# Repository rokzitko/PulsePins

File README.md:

# PulsePins Pulse Sequencer

PulsePins is an open-hardware FPGA pulse sequencer for laboratory timing and digital control. The released DE10-Nano design provides 32 digital outputs and a 10 ns programmable time step at a 100 MHz streamer clock. Use it for triggers, gates, digital buses, and DAC or DDS control; it does not generate analog or RF waveforms directly.

## Start here

Choose the path that matches what you want to do first:

| Goal | Start here |
| ---- | ---------- |
| Bring up a DE10-Nano | [Quick start](docs/docs/quick_start.md) |
| Choose a command or API | [Tool chooser](docs/docs/choose_tool.md) |
| Follow a complete lab workflow | [Worked examples](docs/docs/examples.md) |
| Understand the sequencer | [Sequencer model](docs/docs/sequencer_model.md) |
| Modify or extend PulsePins | [Hacking guide](HACKING.md) and [extension cookbook](docs/docs/extension_cookbook.md) |

## At a glance

| Item | Released DE10-Nano design |
| ---- | ------------------------- |
| Digital output | 32-bit bus, 3.3 V LVTTL |
| Timing | 10 ns programmable time step at a 100 MHz streamer clock |
| Sequence delivery | HPS-driven FIFO or memory-backed DMA transfers up to 512 MB |
| Control | Command-line tools, C++, Python, SCPI-style TCP, and a browser interface |
| Checks | FPGA readback encoder, CRC and FIFO diagnostics, and board self-tests |
| Design files | SystemVerilog/Verilog RTL, software, and KiCad sources under the MIT License |

## Documentation

[User and reference manual](http://auger.ijs.si/pulsepins/site/) ([source](docs/docs/index.md))

Useful contributor documents:

* [Hacking guide](HACKING.md)
* [Contribution guide](CONTRIBUTING.md)
* [Build and deployment](docs/docs/build.md)
* [Development guide](docs/docs/hacking.md)

## Recipes

Reusable command examples for the PulsePins command-line tools are stored in [`recipes/`](recipes/).
These files are separate from `tests/` so test executables and example command invocations are easier to find.

## License

This project is released under the MIT License. You may use, copy, modify, merge, publish, distribute, sublicense,
and/or sell the software and FPGA firmware (including RTL sources and generated bitstreams), including in commercial
and closed-source products. The only conditions are that you preserve the original copyright and license notice in all
substantial portions of the software/firmware, and that the software and firmware are provided “as is”, without any
warranty or liability on the part of the authors.

If you use PulsePins in scientific work, please cite:

> R. Žitko, *PulsePins: Open-hardware digital pulse sequencer for time-resolved experiments*, Zenodo (2025), [doi:10.5281/zenodo.17903233](https://doi.org/10.5281/zenodo.17903233).

### BibTeX

```bibtex
@misc{pulsepins_1_0,
  author       = {Žitko, Rok},
  title        = {PulsePins: Open-hardware digital pulse sequencer for time-resolved experiments},
  year         = {2025},
  publisher    = {Zenodo},
  version      = {1.0},
  doi          = {10.5281/zenodo.17903233},
  url          = {https://doi.org/10.5281/zenodo.17903233}
}
```

## Acknowledgments

This project incorporates code from the project [rsyocto](https://github.com/robseb/rsyocto) (c) Robin Sebastian, licensed under the MIT License.
See `third_party/rsyocto/LICENSE` for details.

[Rok Zitko](http://auger.ijs.si/nano), [rok.zitko@ijs.si](mailto:rok.zitko+pulsepins@ijs.si), 2025

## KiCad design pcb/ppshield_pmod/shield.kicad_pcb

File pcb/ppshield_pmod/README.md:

## PulsePins shield with Pmod ports

Features:

 -   all signals on connectors have ESD protection diodes
 -   SMA connectors for external clock and for pulse-per-second (PPS) signals; monitoring LED for PPS signal; optional built-in 50 Ω terminators
 -   SMA connector for one trigger signal; it is connected to a fast comparator with a tunable reference voltage; optional 50 Ω terminator; monitoring LED
 -   two output signals, Q0 and Q1, are buffered and wired to SMA connectors; monitoring LEDs
 -   Status LEDs: trigger armed, trigger activated, done, buffer error
 -   Activity & heartbeat LEDs
 -   Qwiic I2C connector for external modules
 -   Optional temperature monitor (I2C interface)
 -   Optional 16-bit DAC (I2C interface) with a separate low-noise power supply (a possible application is frequency tuning of an OCXO; with PPS from a GNSS receiver, this can form a simple GPS-disciplined oscillator (GPSDO))
 -   Test points for troubleshooting

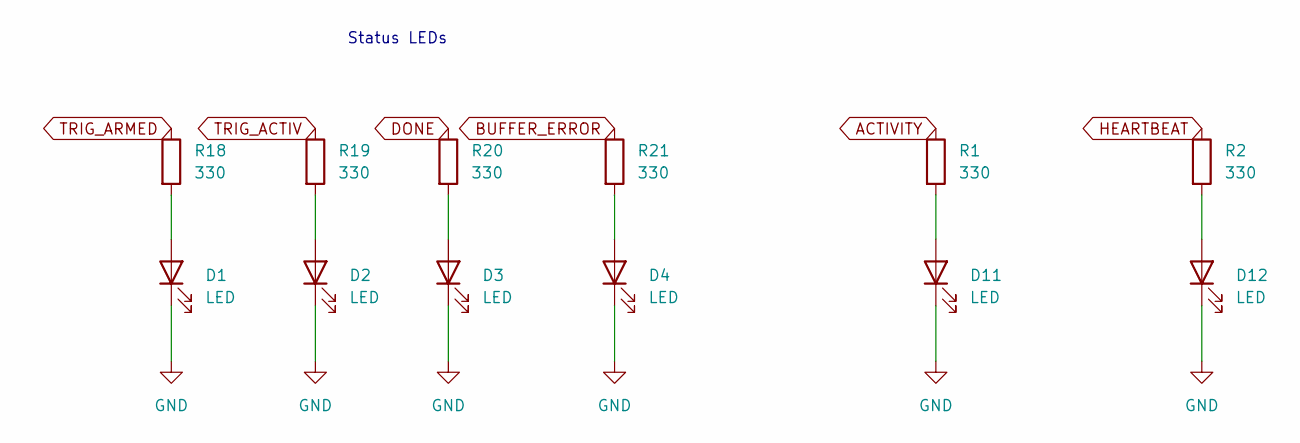
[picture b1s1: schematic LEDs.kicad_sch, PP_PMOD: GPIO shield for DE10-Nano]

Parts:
D1, D2, D3, D4, D11, D12: LED; LED_0603_1608Metric_Pad1.05x0.95mm_HandSolder
R1, R2, R18, R19, R20, R21: 330; R_0603_1608Metric_Pad0.98x0.95mm_HandSolder

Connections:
ACTIVITY: R1.1; also elsewhere on the board
BUFFER_ERROR: R21.1; also elsewhere on the board
DONE: R20.1; also elsewhere on the board
GND: D1.1 (K), D2.1 (K), D3.1 (K), D4.1 (K), D11.1 (K), D12.1 (K); also elsewhere on the board
HEARTBEAT: R2.1; also elsewhere on the board
unnamed: D1.2 (A), R18.2
unnamed: D2.2 (A), R19.2
unnamed: D3.2 (A), R20.2
unnamed: D4.2 (A), R21.2
unnamed: D11.2 (A), R1.2
unnamed: D12.2 (A), R2.2
TRIG_ACTIV: R19.1; also elsewhere on the board
TRIG_ARMED: R18.1; also elsewhere on the board

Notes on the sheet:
Status LEDs

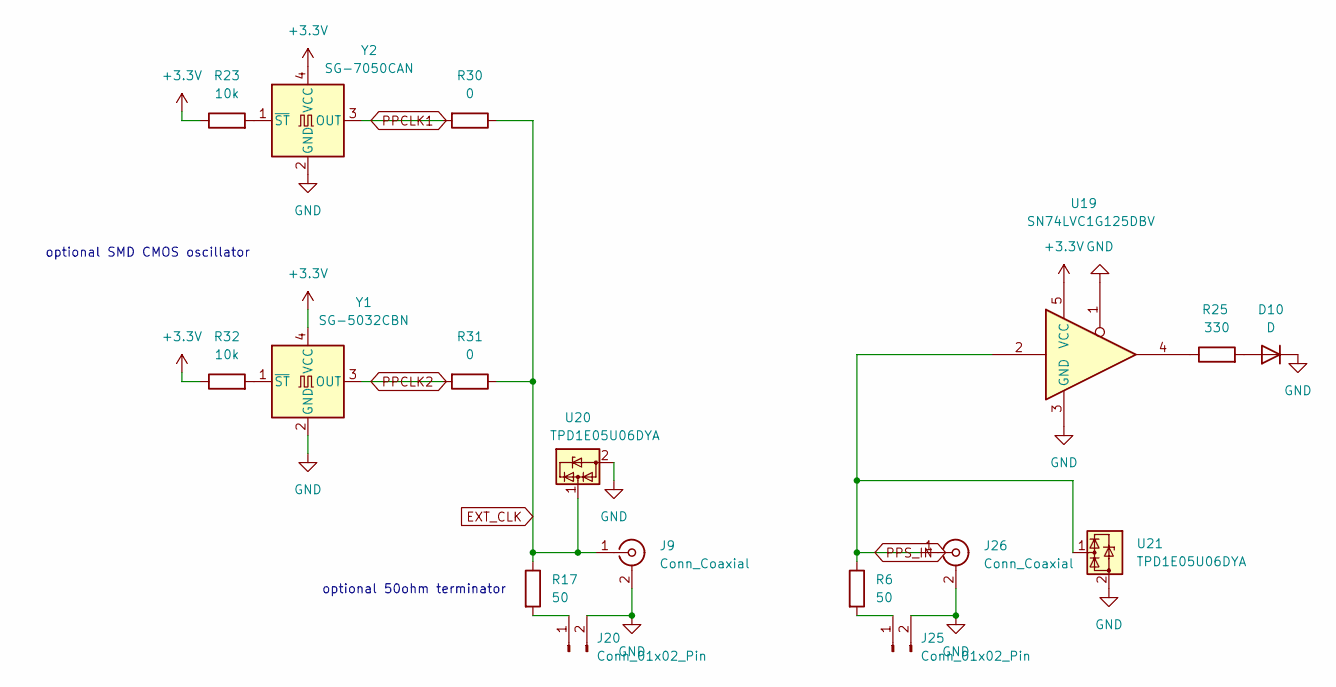
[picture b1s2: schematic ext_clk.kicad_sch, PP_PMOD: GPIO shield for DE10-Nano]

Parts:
D10: D; LED_0603_1608Metric_Pad1.05x0.95mm_HandSolder
J9, J26: Conn_Coaxial; SMA_Amphenol_132134-16_Vertical
J20, J25: Conn_01x02_Pin; PinHeader_1x02_P2.00mm_Vertical
R6, R17: 50; R_0603_1608Metric_Pad0.98x0.95mm_HandSolder
R23, R32: 10k; R_0603_1608Metric_Pad0.98x0.95mm_HandSolder
R25: 330; R_0603_1608Metric_Pad0.98x0.95mm_HandSolder
R30, R31: 0; R_0402_1005Metric_Pad0.72x0.64mm_HandSolder
U19: SN74LVC1G125DBV; SOT-23-5
U20, U21: TPD1E05U06DYA; D_SOD-523
Y1: SG-5032CBN; Crystal_SMD_5032-4Pin_5.0x3.2mm
Y2: SG-7050CAN; Oscillator_SMD_SeikoEpson_SG8002CA-4Pin_7.0x5.0mm

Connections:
+3.3V: R23.1, R32.1, U19.5 (VCC), Y1.4 (VCC), Y2.4 (VCC); also elsewhere on the board
EXT_CLK: J9.1 (In), R17.1, R30.1, R31.1, U20.1 (I/O); also elsewhere on the board
GND: D10.1 (K), J9.2 (Ext), J20.2, J25.2, J26.2 (Ext), U19.1, U19.3 (GND), U20.2 (GND), U21.2 (GND), Y1.2 (GND), Y2.2 (GND); also elsewhere on the board
unnamed: D10.2 (A), R25.2
unnamed: J20.1, R17.2
unnamed: J25.1, R6.2
unnamed: R25.1, U19.4
unnamed: R32.2, Y1.1 (~ST)
unnamed: R23.2, Y2.1 (~ST)
PPCLK1: R30.2, Y2.3 (OUT); also elsewhere on the board
PPCLK2: R31.2, Y1.3 (OUT); also elsewhere on the board
PPS_IN: J26.1 (In), R6.1, U19.2, U21.1 (I/O); also elsewhere on the board

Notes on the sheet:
optional 50ohm terminator
optional SMD CMOS oscillator

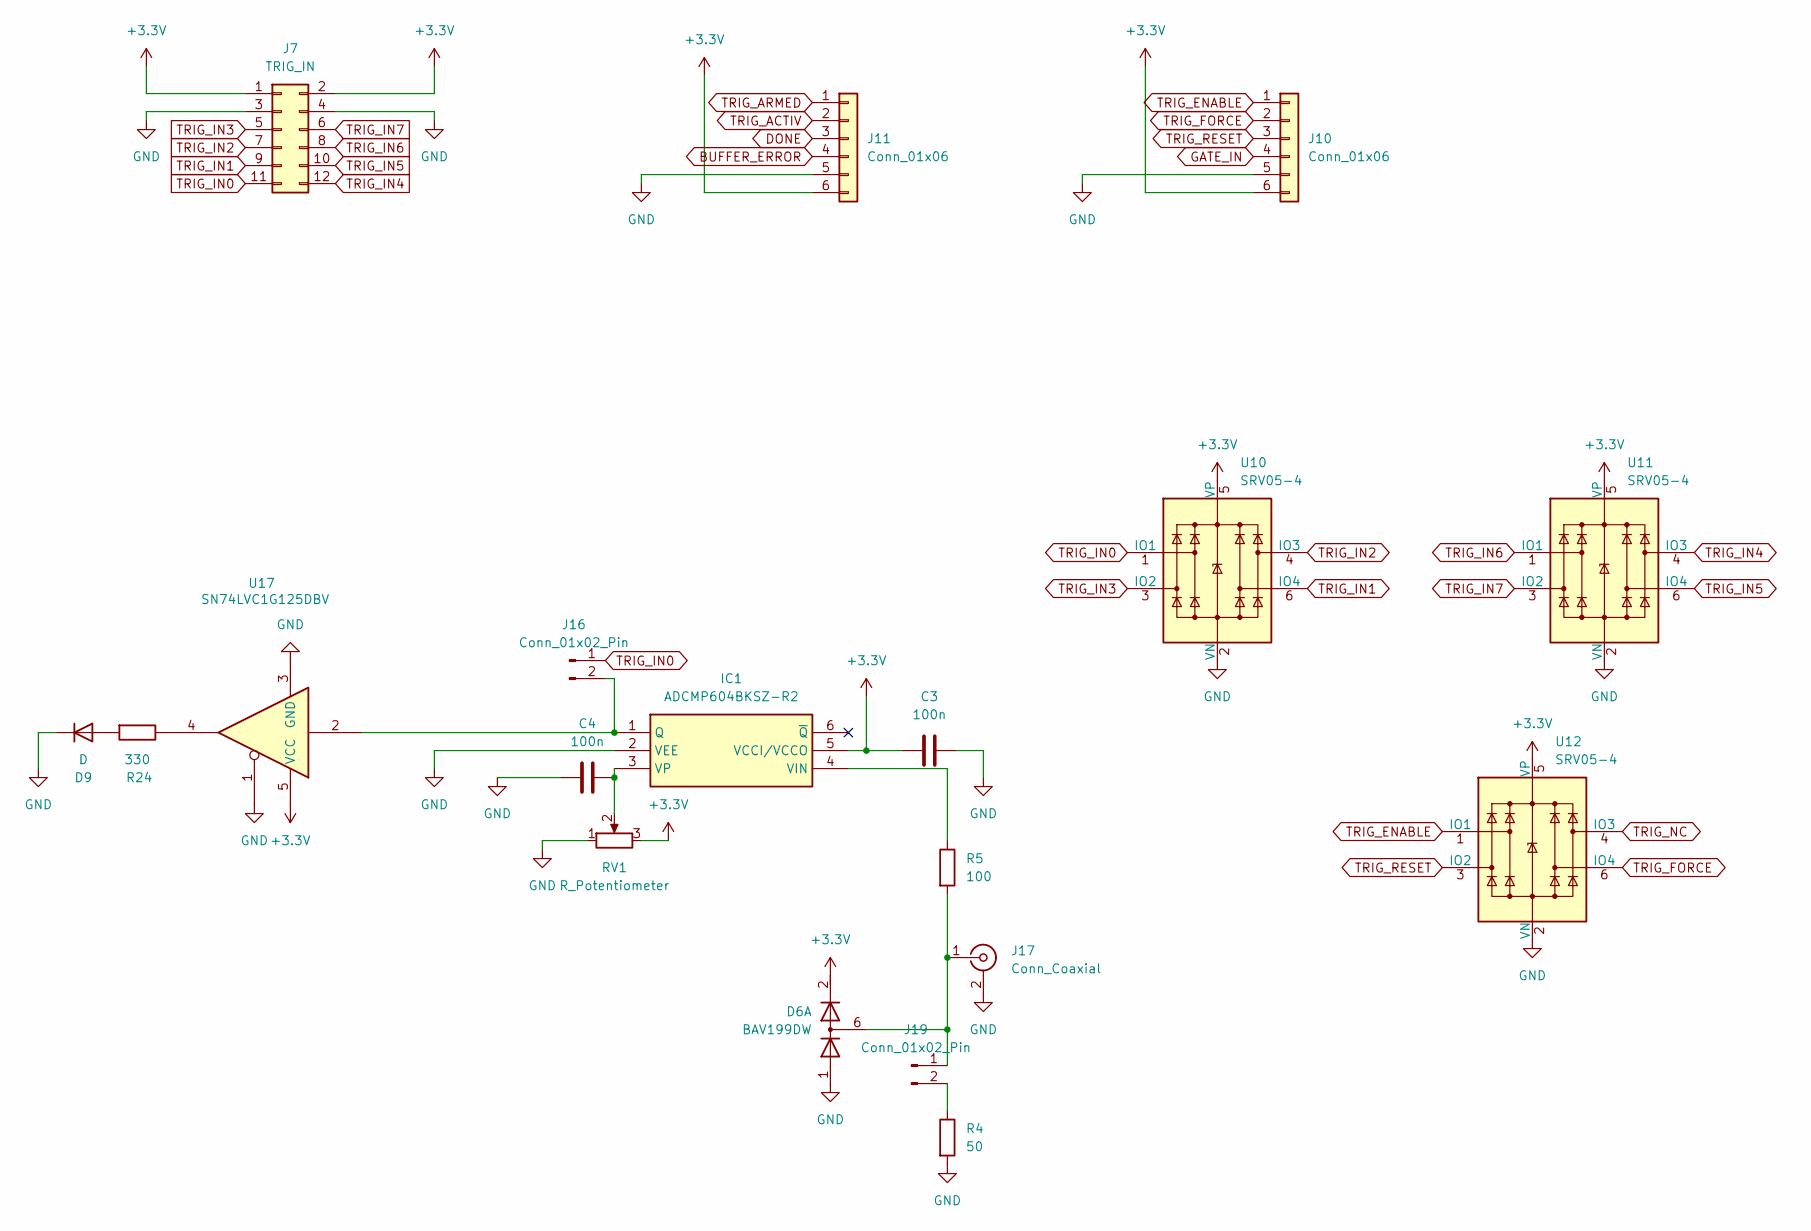
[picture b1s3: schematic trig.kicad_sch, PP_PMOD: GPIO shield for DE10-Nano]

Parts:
C3, C4: 100n; C_0603_1608Metric_Pad1.08x0.95mm_HandSolder
D6: BAV199DW; SOT-363_SC-70-6
D9: D; LED_0603_1608Metric_Pad1.05x0.95mm_HandSolder
IC1: ADCMP604BKSZ-R2; SOT-363_SC-70-6_Handsoldering; Manufacturer_Part_Number ADCMP604BKSZ-R2; Mouser Part Number 584-ADCMP604BKSZ-R2
J7: TRIG_IN; PinSocket_2x06_P2.54mm_Horizontal
J10, J11: Conn_01x06; PinSocket_1x06_P2.54mm_Vertical
J16: Conn_01x02_Pin; PinHeader_1x02_P2.54mm_Vertical
J17: Conn_Coaxial; SMA_Amphenol_132134-16_Vertical
J19: Conn_01x02_Pin; PinHeader_1x02_P2.00mm_Vertical
R4: 50; R_0603_1608Metric_Pad0.98x0.95mm_HandSolder
R5: 100; R_0603_1608Metric_Pad0.98x0.95mm_HandSolder
R24: 330; R_0603_1608Metric_Pad0.98x0.95mm_HandSolder
RV1: R_Potentiometer; Potentiometer_Bourns_3266P_Horizontal
U10, U11, U12: SRV05-4; SOT-23-6
U17: SN74LVC1G125DBV; SOT-23-5

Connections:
+3.3V: C3.1, D6.2 (K2), IC1.5 (VCCI/VCCO), J7.1, J7.2, J10.6, J11.6, RV1.3, U10.5 (VP), U11.5 (VP), U12.5 (VP), U17.5 (VCC); also elsewhere on the board
BUFFER_ERROR: J11.4; also elsewhere on the board
DONE: J11.3; also elsewhere on the board
GND: C3.2, C4.1, D6.1 (A1), D9.1 (K), IC1.2 (VEE), J7.3, J7.4, J10.5, J11.5, J17.2 (Ext), R4.2, RV1.1, U10.2 (VN), U11.2 (VN), U12.2 (VN), U17.1, U17.3 (GND); also elsewhere on the board
unnamed: D6.6 (K3A4), J17.1 (In), J19.1, R5.2
unnamed: D9.2 (A), R24.2
unnamed: IC1.1 (Q), J16.2, U17.2
unnamed: IC1.4 (VIN), R5.1
unnamed: C4.2, IC1.3 (VP), RV1.2
unnamed: J19.2, R4.1
unnamed: R24.1, U17.4
TRIG_ACTIV: J11.2; also elsewhere on the board
TRIG_ARMED: J11.1; also elsewhere on the board
TRIG_IN0: J7.11, J16.1, U10.1 (IO1); also elsewhere on the board
TRIG_IN1: J7.9, U10.6 (IO4); also elsewhere on the board
TRIG_IN2: J7.7, U10.4 (IO3); also elsewhere on the board
TRIG_IN3: J7.5, U10.3 (IO2); also elsewhere on the board
TRIG_IN4: J7.12, U11.4 (IO3); also elsewhere on the board
TRIG_IN5: J7.10, U11.6 (IO4); also elsewhere on the board
TRIG_IN6: J7.8, U11.1 (IO1); also elsewhere on the board
TRIG_IN7: J7.6, U11.3 (IO2); also elsewhere on the board
TRIG_RESET: J10.3, U12.3 (IO2); also elsewhere on the board

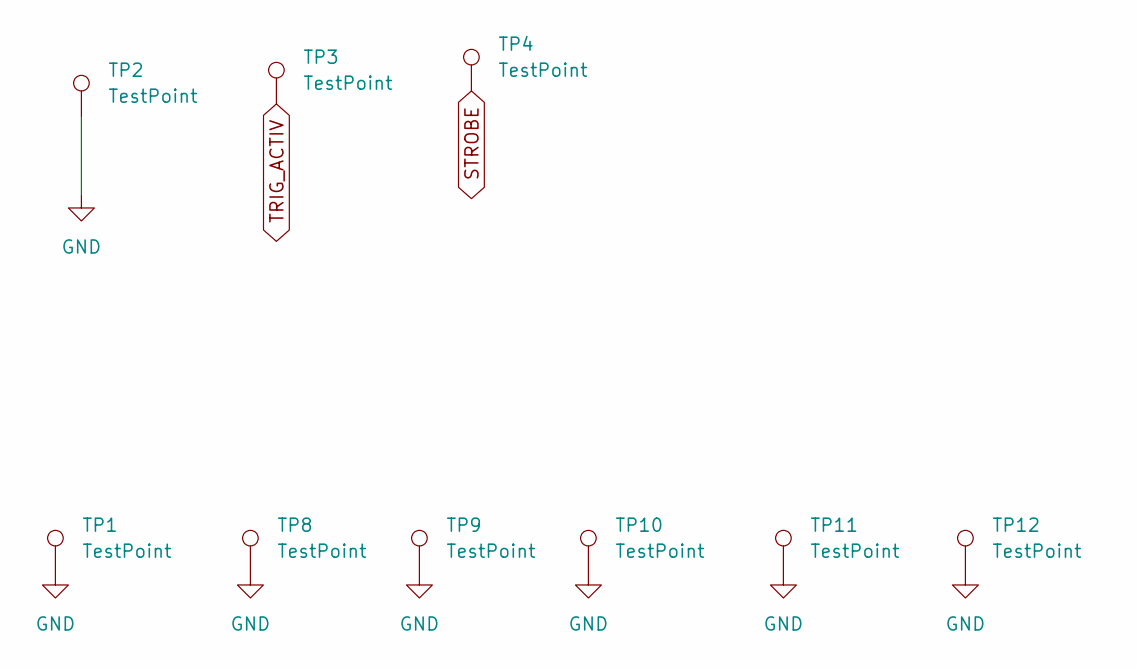
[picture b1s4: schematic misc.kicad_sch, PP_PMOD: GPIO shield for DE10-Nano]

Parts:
TP1, TP8, TP9, TP10, TP11, TP12: TestPoint; TestPoint_THTPad_D2.0mm_Drill1.0mm
TP2, TP3, TP4: TestPoint; TestPoint_Loop_D1.80mm_Drill1.0mm_Beaded

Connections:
GND: TP1.1, TP2.1, TP8.1, TP9.1, TP10.1, TP11.1, TP12.1; also elsewhere on the board
STROBE: TP4.1; also elsewhere on the board
TRIG_ACTIV: TP3.1; also elsewhere on the board

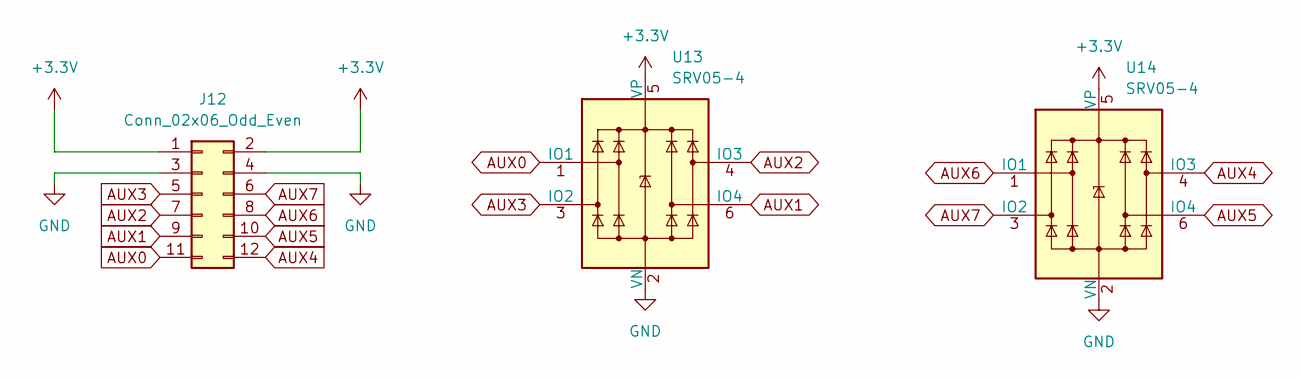
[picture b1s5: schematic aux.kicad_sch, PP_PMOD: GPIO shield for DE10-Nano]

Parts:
J12: Conn_02x06_Odd_Even; PinSocket_2x06_P2.54mm_Horizontal
U13, U14: SRV05-4; SOT-23-6

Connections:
+3.3V: J12.1, J12.2, U13.5 (VP), U14.5 (VP); also elsewhere on the board
AUX0: J12.11, U13.1 (IO1); also elsewhere on the board
AUX1: J12.9, U13.6 (IO4); also elsewhere on the board
AUX2: J12.7, U13.4 (IO3); also elsewhere on the board
AUX3: J12.5, U13.3 (IO2); also elsewhere on the board
AUX4: J12.12, U14.4 (IO3); also elsewhere on the board
AUX5: J12.10, U14.6 (IO4); also elsewhere on the board
AUX6: J12.8, U14.1 (IO1); also elsewhere on the board
AUX7: J12.6, U14.3 (IO2); also elsewhere on the board
GND: J12.3, J12.4, U13.2 (VN), U14.2 (VN); also elsewhere on the board

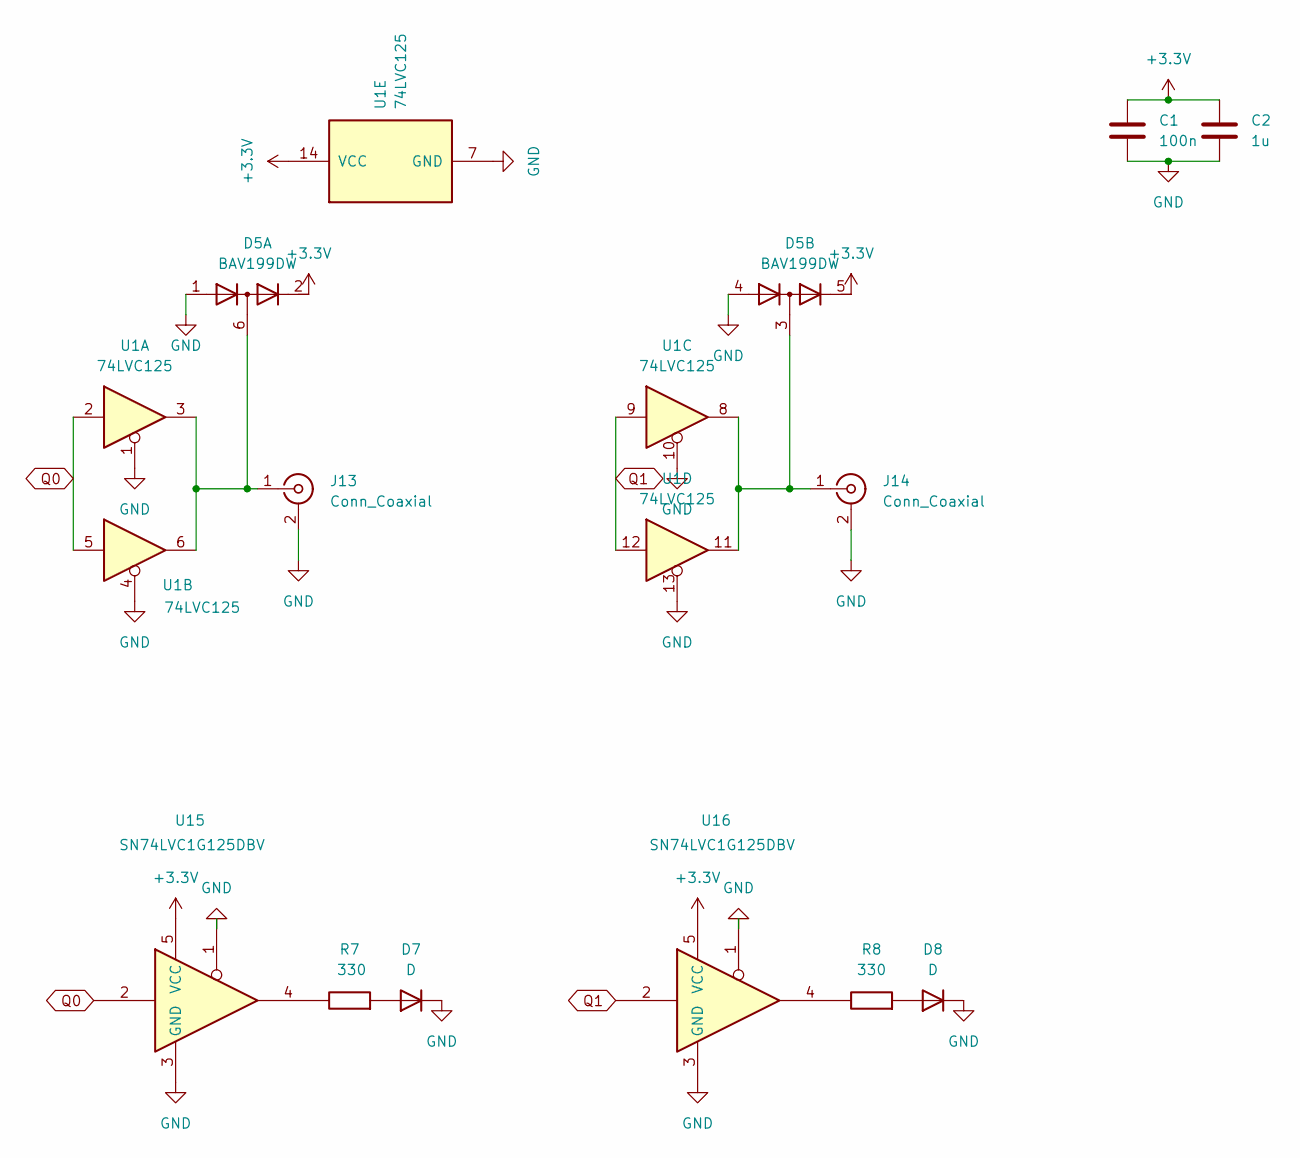
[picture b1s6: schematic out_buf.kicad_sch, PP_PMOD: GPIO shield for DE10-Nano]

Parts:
C1: 100n; C_0603_1608Metric_Pad1.08x0.95mm_HandSolder
C2: 1u; C_0603_1608Metric_Pad1.08x0.95mm_HandSolder
D5: BAV199DW; SOT-363_SC-70-6
D7, D8: D; LED_0603_1608Metric_Pad1.05x0.95mm_HandSolder
J13, J14: Conn_Coaxial; SMA_Amphenol_132134-16_Vertical
R7, R8: 330; R_0603_1608Metric_Pad0.98x0.95mm_HandSolder
U1: 74LVC125; SOIC-14_3.9x8.7mm_P1.27mm
U15, U16: SN74LVC1G125DBV; SOT-23-5

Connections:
+3.3V: C1.1, C2.1, D5.2 (K2), D5.5 (K4), U1.14 (VCC), U15.5 (VCC), U16.5 (VCC); also elsewhere on the board
GND: C1.2, C2.2, D5.1 (A1), D5.4 (A3), D7.1 (K), D8.1 (K), J13.2 (Ext), J14.2 (Ext), U1.1, U1.4, U1.7 (GND), U1.10, U1.13, U15.1, U15.3 (GND), U16.1, U16.3 (GND); also elsewhere on the board
unnamed: D5.6 (K3A4), J13.1 (In), U1.3, U1.6
unnamed: D5.3 (K1A2), J14.1 (In), U1.8, U1.11
unnamed: D7.2 (A), R7.2
unnamed: D8.2 (A), R8.2
unnamed: R7.1, U15.4
unnamed: R8.1, U16.4
Q0: U1.2, U1.5, U15.2; also elsewhere on the board
Q1: U1.9, U1.12, U16.2; also elsewhere on the board

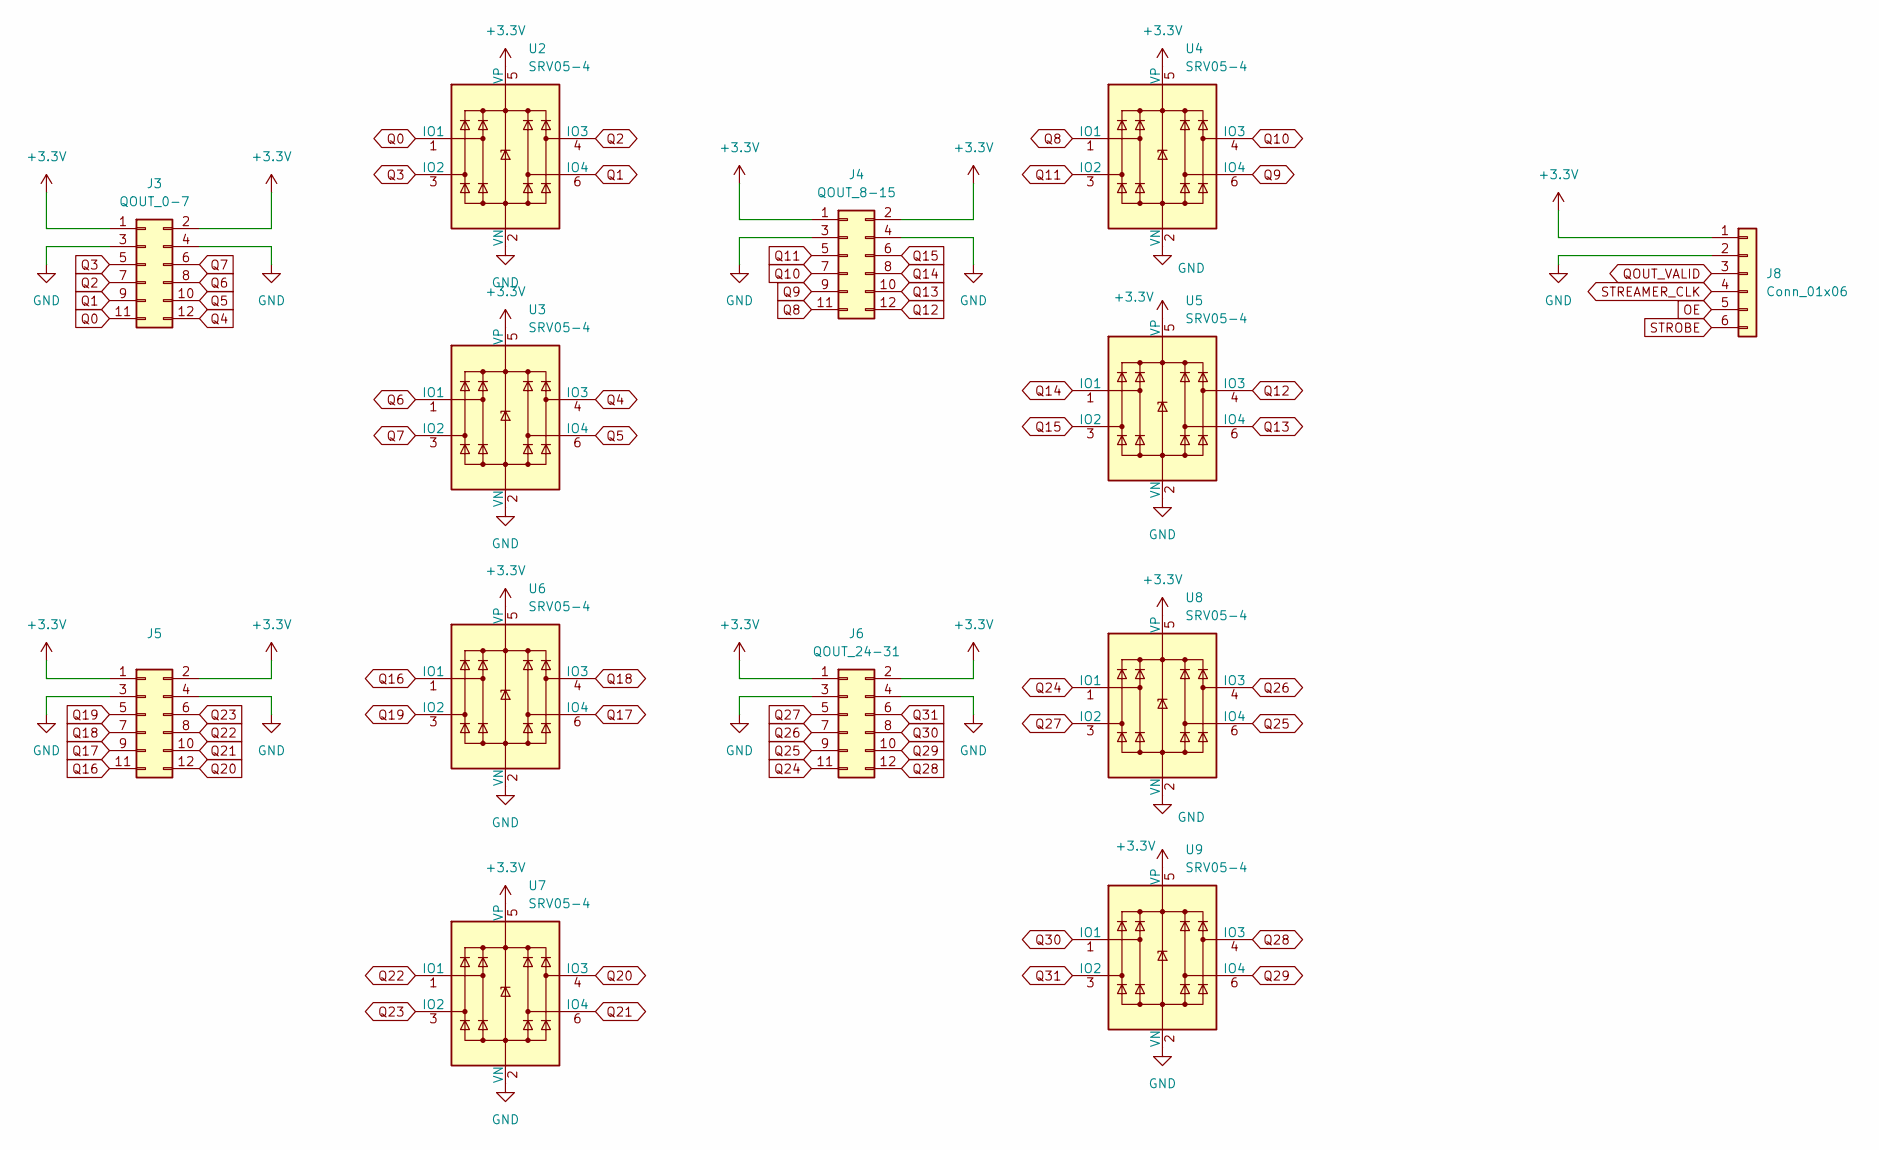
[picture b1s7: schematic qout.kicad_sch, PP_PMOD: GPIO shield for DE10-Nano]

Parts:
J3: QOUT_0-7; PinSocket_2x06_P2.54mm_Horizontal
J4: QOUT_8-15; PinSocket_2x06_P2.54mm_Horizontal
J5: QOUT_16-23; PinSocket_2x06_P2.54mm_Horizontal
J6: QOUT_24-31; PinSocket_2x06_P2.54mm_Horizontal
J8: Conn_01x06; PinSocket_1x06_P2.54mm_Horizontal
U2, U3, U4, U5, U6, U7, U8, U9: SRV05-4; SOT-23-6

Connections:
+3.3V: J3.1, J3.2, J4.1, J4.2, J5.1, J5.2, J6.1, J6.2, J8.1, U2.5 (VP), U3.5 (VP), U4.5 (VP), U5.5 (VP), U6.5 (VP), U7.5 (VP), U8.5 (VP), U9.5 (VP); also elsewhere on the board
GND: J3.3, J3.4, J4.3, J4.4, J5.3, J5.4, J6.3, J6.4, J8.2, U2.2 (VN), U3.2 (VN), U4.2 (VN), U5.2 (VN), U6.2 (VN), U7.2 (VN), U8.2 (VN), U9.2 (VN); also elsewhere on the board
OE: J8.5; also elsewhere on the board
Q0: J3.11, U2.1 (IO1); also elsewhere on the board
Q1: J3.9, U2.6 (IO4); also elsewhere on the board
Q2: J3.7, U2.4 (IO3); also elsewhere on the board
Q3: J3.5, U2.3 (IO2); also elsewhere on the board
Q4: J3.12, U3.4 (IO3); also elsewhere on the board
Q5: J3.10, U3.6 (IO4); also elsewhere on the board
Q6: J3.8, U3.1 (IO1); also elsewhere on the board
Q7: J3.6, U3.3 (IO2); also elsewhere on the board
Q8: J4.11, U4.1 (IO1); also elsewhere on the board
Q9: J4.9, U4.6 (IO4); also elsewhere on the board
Q10: J4.7, U4.4 (IO3); also elsewhere on the board
Q11: J4.5, U4.3 (IO2); also elsewhere on the board
Q12: J4.12, U5.4 (IO3); also elsewhere on the board
Q13: J4.10, U5.6 (IO4); also elsewhere on the board
Q14: J4.8, U5.1 (IO1); also elsewhere on the board
Q15: J4.6, U5.3 (IO2); also elsewhere on the board
Q16: J5.11, U6.1 (IO1); also elsewhere on the board
Q17: J5.9, U6.6 (IO4); also elsewhere on the board
Q18: J5.7, U6.4 (IO3); also elsewhere on the board
Q19: J5.5, U6.3 (IO2); also elsewhere on the board
Q20: J5.12, U7.4 (IO3); also elsewhere on the board
Q21: J5.10, U7.6 (IO4); also elsewhere on the board
Q22: J5.8, U7.1 (IO1); also elsewhere on the board
Q23: J5.6, U7.3 (IO2); also elsewhere on the board
Q24: J6.11, U8.1 (IO1); also elsewhere on the board
Q25: J6.9, U8.6 (IO4); also elsewhere on the board
Q26: J6.7, U8.4 (IO3); also elsewhere on the board
Q27: J6.5, U8.3 (IO2); also elsewhere on the board
Q28: J6.12, U9.4 (IO3); also elsewhere on the board
Q29: J6.10, U9.6 (IO4); also elsewhere on the board
Q30: J6.8, U9.1 (IO1); also elsewhere on the board
Q31: J6.6, U9.3 (IO2); also elsewhere on the board
QOUT_VALID: J8.3; also elsewhere on the board
STREAMER_CLK: J8.4; also elsewhere on the board
STROBE: J8.6; also elsewhere on the board

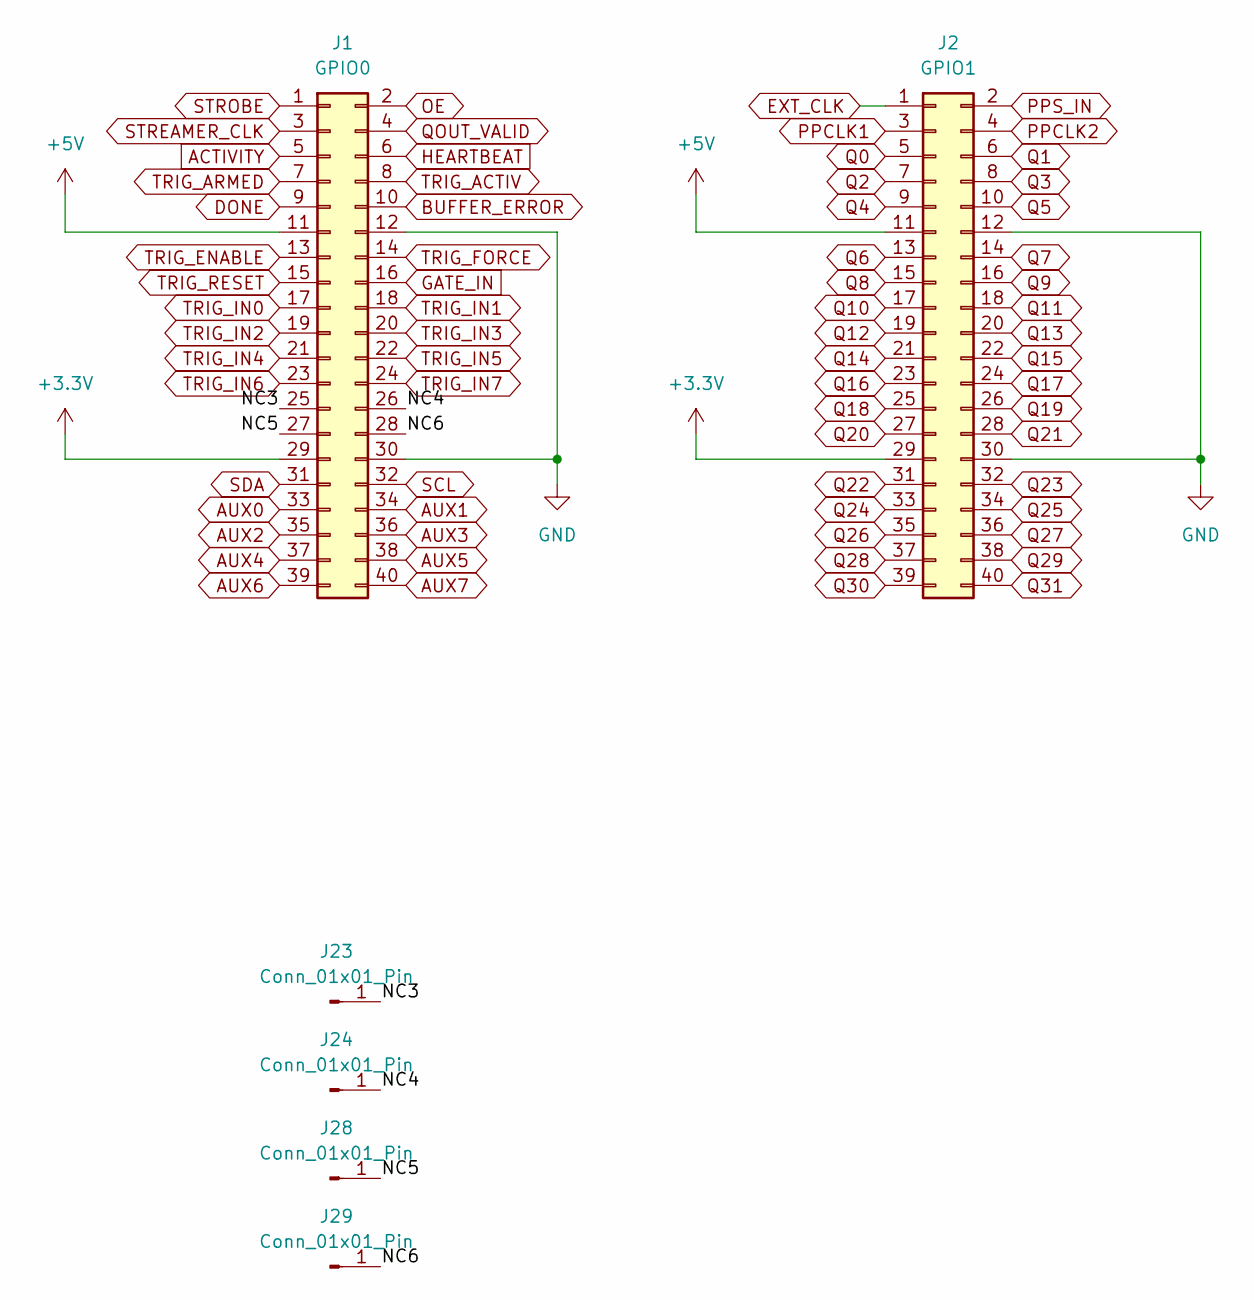
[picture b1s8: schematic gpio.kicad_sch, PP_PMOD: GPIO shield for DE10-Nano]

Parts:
J1: GPIO0; PinSocket_2x20_P2.54mm_Vertical
J2: GPIO1; PinSocket_2x20_P2.54mm_Vertical
J23, J24, J28, J29: Conn_01x01_Pin; TestPoint_THTPad_1.5x1.5mm_Drill0.7mm

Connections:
+3.3V: J1.29, J2.29; also elsewhere on the board
+5V: J1.11, J2.11; also elsewhere on the board
/GPIO/NC3: J1.25, J23.1
/GPIO/NC4: J1.26, J24.1
/GPIO/NC5: J1.27, J28.1
/GPIO/NC6: J1.28, J29.1
ACTIVITY: J1.5; also elsewhere on the board
AUX0: J1.33; also elsewhere on the board
AUX1: J1.34; also elsewhere on the board
AUX2: J1.35; also elsewhere on the board
AUX3: J1.36; also elsewhere on the board
AUX4: J1.37; also elsewhere on the board
AUX5: J1.38; also elsewhere on the board
AUX6: J1.39; also elsewhere on the board
AUX7: J1.40; also elsewhere on the board
BUFFER_ERROR: J1.10; also elsewhere on the board
DONE: J1.9; also elsewhere on the board
EXT_CLK: J2.1; also elsewhere on the board
GND: J1.12, J1.30, J2.12, J2.30; also elsewhere on the board
HEARTBEAT: J1.6; also elsewhere on the board
OE: J1.2; also elsewhere on the board
PPCLK1: J2.3; also elsewhere on the board
PPCLK2: J2.4; also elsewhere on the board
PPS_IN: J2.2; also elsewhere on the board
Q0: J2.5; also elsewhere on the board
Q1: J2.6; also elsewhere on the board
Q2: J2.7; also elsewhere on the board
Q3: J2.8; also elsewhere on the board
Q4: J2.9; also elsewhere on the board
Q5: J2.10; also elsewhere on the board
Q6: J2.13; also elsewhere on the board
Q7: J2.14; also elsewhere on the board
Q8: J2.15; also elsewhere on the board
Q9: J2.16; also elsewhere on the board
Q10: J2.17; also elsewhere on the board
Q11: J2.18; also elsewhere on the board
Q12: J2.19; also elsewhere on the board
Q13: J2.20; also elsewhere on the board
Q14: J2.21; also elsewhere on the board
Q15: J2.22; also elsewhere on the board
Q16: J2.23; also elsewhere on the board
Q17: J2.24; also elsewhere on the board
Q18: J2.25; also elsewhere on the board
Q19: J2.26; also elsewhere on the board
Q20: J2.27; also elsewhere on the board
Q21: J2.28; also elsewhere on the board
Q22: J2.31; also elsewhere on the board
Q23: J2.32; also elsewhere on the board
Q24: J2.33; also elsewhere on the board
Q25: J2.34; also elsewhere on the board
Q26: J2.35; also elsewhere on the board
Q27: J2.36; also elsewhere on the board
Q28: J2.37; also elsewhere on the board
Q29: J2.38; also elsewhere on the board
Q30: J2.39; also elsewhere on the board
Q31: J2.40; also elsewhere on the board
QOUT_VALID: J1.4; also elsewhere on the board
SCL: J1.32; also elsewhere on the board
SDA: J1.31; also elsewhere on the board
STREAMER_CLK: J1.3; also elsewhere on the board
STROBE: J1.1; also elsewhere on the board
TRIG_ACTIV: J1.8; also elsewhere on the board
TRIG_ARMED: J1.7; also elsewhere on the board
TRIG_IN0: J1.17; also elsewhere on the board
TRIG_IN1: J1.18; also elsewhere on the board
TRIG_IN2: J1.19; also elsewhere on the board
TRIG_IN3: J1.20; also elsewhere on the board
TRIG_IN4: J1.21; also elsewhere on the board
TRIG_IN5: J1.22; also elsewhere on the board
TRIG_IN6: J1.23; also elsewhere on the board
TRIG_IN7: J1.24; also elsewhere on the board
TRIG_RESET: J1.15; also elsewhere on the board

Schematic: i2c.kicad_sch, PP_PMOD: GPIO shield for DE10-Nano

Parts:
C5, C6, C9: 100n; C_0603_1608Metric_Pad1.08x0.95mm_HandSolder
C7: 10n; C_0603_1608Metric_Pad1.08x0.95mm_HandSolder
C8, C11: 10uF; C_0805_2012Metric_Pad1.18x1.45mm_HandSolder
C10: 1u; C_0603_1608Metric_Pad1.08x0.95mm_HandSolder
C12: 100n; R_0603_1608Metric_Pad0.98x0.95mm_HandSolder
FB1: MZ1608-601Y; L_0603_1608Metric_Pad1.05x0.95mm_HandSolder
J18: Conn_01x04_Pin; JST_SH_SM04B-SRSS-TB_1x04-1MP_P1.00mm_Horizontal
J27: Conn_01x02_Socket; JST_SH_BM02B-SRSS-TB_1x02-1MP_P1.00mm_Vertical
R22: 10k; R_0603_1608Metric_Pad0.98x0.95mm_HandSolder
R26: 0; C_0402_1005Metric_Pad0.74x0.62mm_HandSolder
R27, R28, R29: 0; R_0402_1005Metric_Pad0.72x0.64mm_HandSolder
TP5, TP6, TP7: TestPoint; TestPoint_Pad_D1.0mm
U18: SRV05-4; SOT-23-6
U22: MCP9808_MSOP; MSOP-8_3x3mm_P0.65mm
U23: AD5693RxRM; MSOP-10_3x3mm_P0.5mm
U24: ADP7142ARDZ-3.3; SOIC-8-1EP_3.9x4.9mm_P1.27mm_EP2.29x3mm

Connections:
+3.3V: C6.1, J18.2, U18.5 (VP), U22.8 (V_{DD}), U23.2 (VLOGIC), U23.3 (~RESET); also elsewhere on the board
+5V: FB1.1; also elsewhere on the board
GND: C5.2, C6.2, C7.2, C8.2, C9.2, C10.2, C11.2, C12.2, J18.1, J27.2, R22.2, R26.2, R27.1, R28.1, R29.1, U18.2 (VN), U18.3 (IO2), U18.4 (IO3), U22.4 (GND), U23.4 (~LDAC), U23.5 (GND), U24.4 (GND), U24.9 (GND); also elsewhere on the board
unnamed: J27.1, TP5.1, U23.10 (VOUT)
unnamed: R27.2, U22.7 (A0)
unnamed: R28.2, U22.6 (A1)
unnamed: R29.2, U22.5 (A2)
unnamed: R22.1, U22.3 (Alert)
unnamed: R26.1, U23.6 (A0)
unnamed: C5.1, C8.1, C9.1, C10.1, TP7.1, U23.1 (VDD), U24.1 (VOUT), U24.2 (VOUT), U24.3 (SENSE/ADJ)
unnamed: C7.1, TP6.1, U23.9 (VREF)
unnamed: C11.1, FB1.2, U24.5 (EN), U24.7 (VIN), U24.8 (VIN)
unnamed: C12.1, U24.6 (SS)
SCL: J18.4, U18.1 (IO1), U22.2 (SCL), U23.7 (SCL); also elsewhere on the board
SDA: J18.3, U18.6 (IO4), U22.1 (SDA), U23.8 (SDA); also elsewhere on the board

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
